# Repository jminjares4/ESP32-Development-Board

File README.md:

# ESP32-Development-Board
## ESP32 2 Layer PCB
* The PCB was developed in KiCad. With the use of https://github.com/wokwi/kicad-jlcpcb-bom-plugin, 
* Use the 'python3' kicad_pos_to_cpl.py to convert KiCad CPL files to JLCPCB 
## BOM
* This folder contains the BOM file for JLCPCB for the ESP32. 
## ESP32 CPL File
* This folder contains the CPL file for ESP32
 ### JLCPCB_File
  *  JLCPCB csv file configuration for ESP32 dev board
 ### KiCad_Pos
  * KiCad default position file for ESP32 dev board

## KiCad ESP32 Schematic

### ESP32 Frontview

### ESP32 Backview

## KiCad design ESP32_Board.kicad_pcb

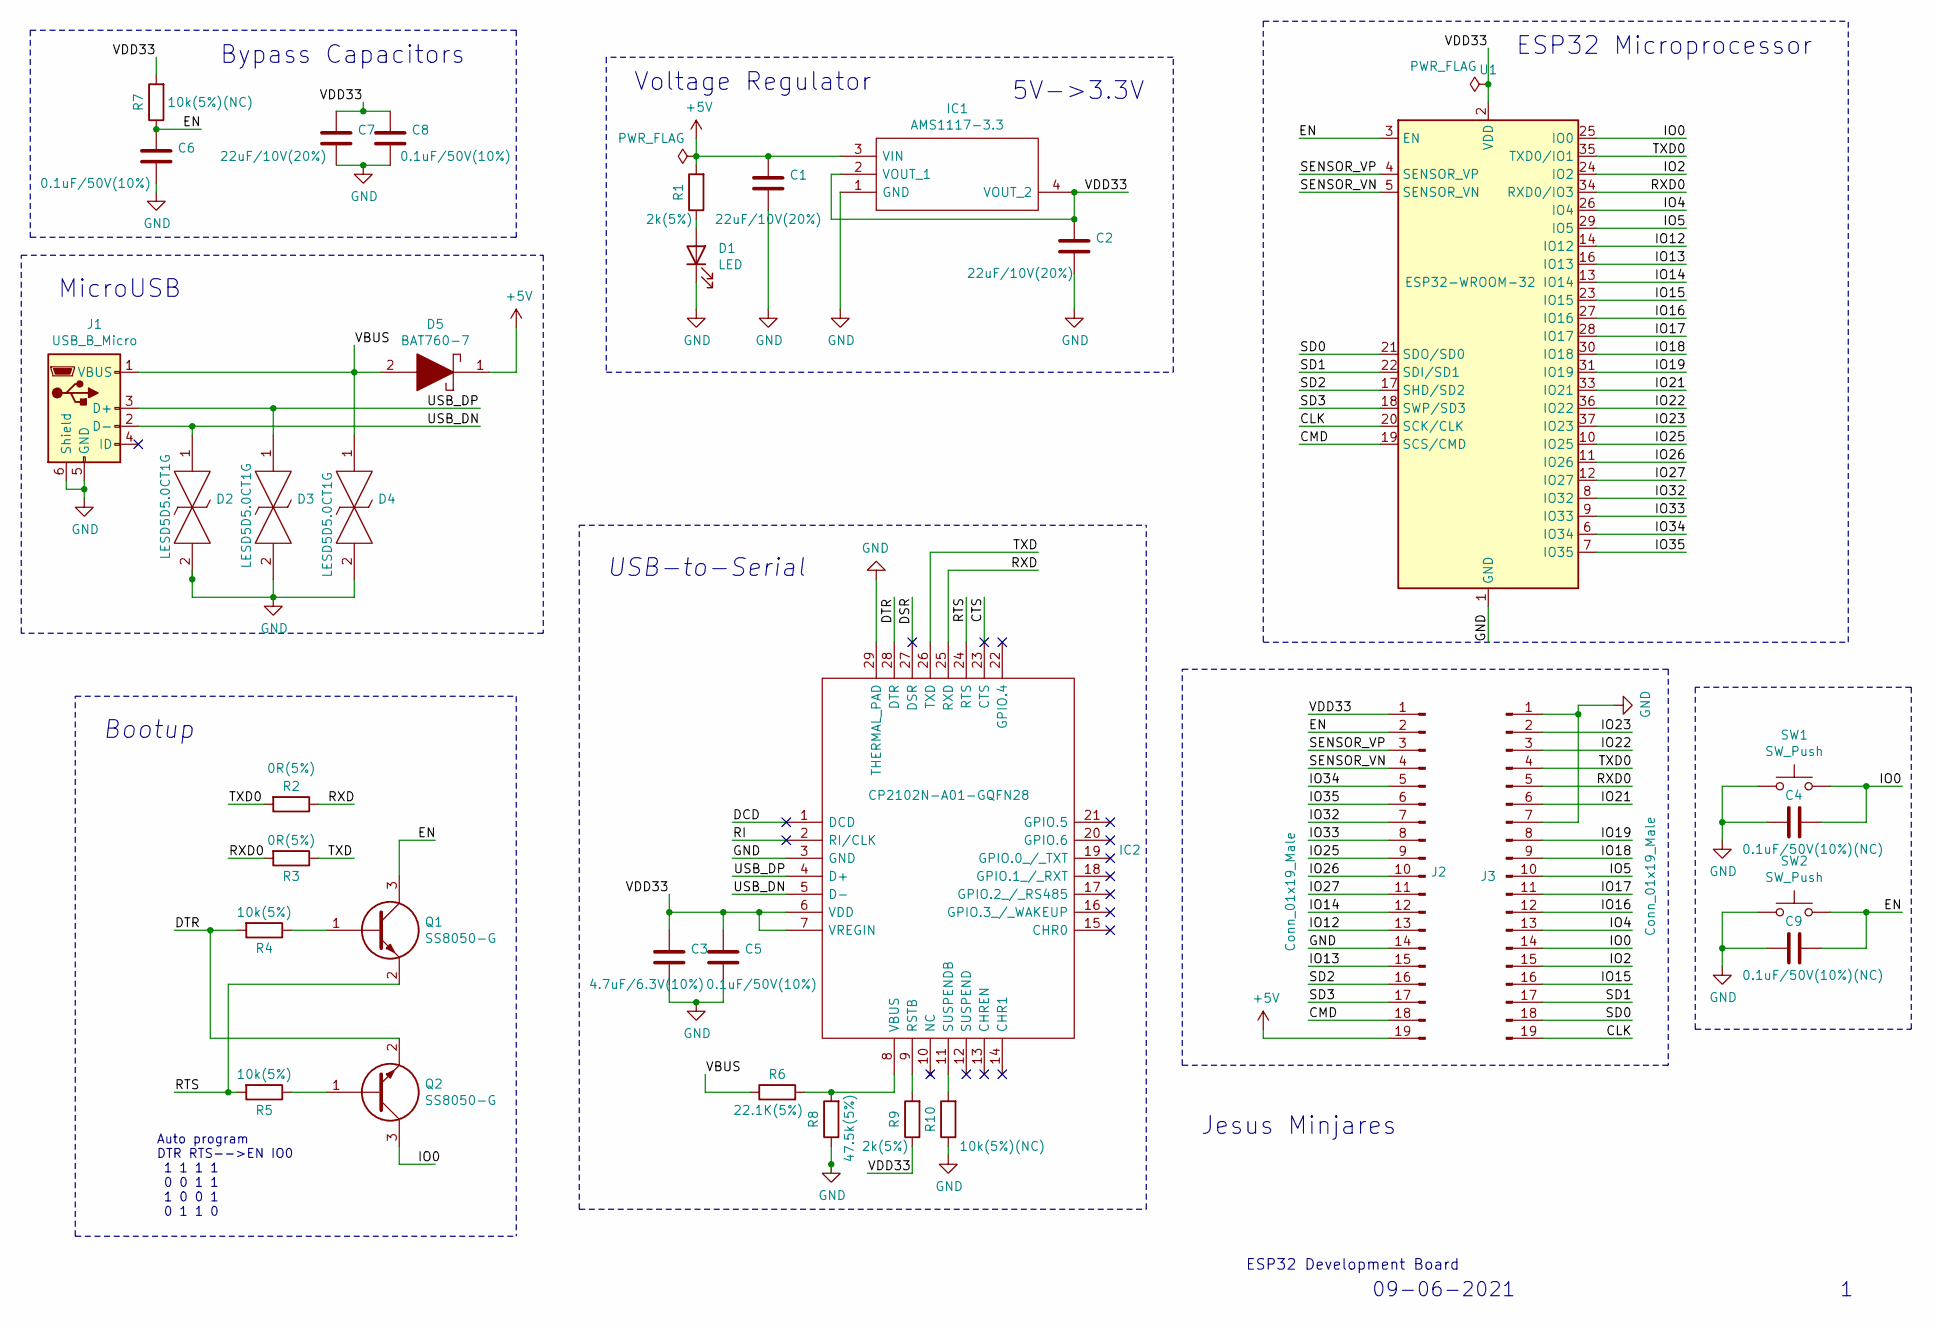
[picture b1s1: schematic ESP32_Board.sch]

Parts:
C1, C2, C7: 22uF/10V(20%); C_0805_2012Metric
C3: 4.7uF/6.3V(10%); C_0805_2012Metric
C4, C9: 0.1uF/50V(10%)(NC); C_0805_2012Metric
C5, C6, C8: 0.1uF/50V(10%); C_0805_2012Metric
D1: LED; LED_0805_2012Metric
D2, D3, D4: LESD5D5.0CT1G; LESD5D50CT1G; Manufacturer_Part_Number LESD5D5.0CT1G
D5: BAT760-7; SOD2513X120N; Manufacturer_Part_Number BAT760-7; Mouser Part Number 621-BAT760-7
IC1: AMS1117-3.3; SOT229P700X180-4N; Manufacturer_Part_Number AMS1117-3.3
IC2: CP2102N-A01-GQFN28; QFN50P500X500X80-29N-D; Manufacturer_Part_Number CP2102N-A01-GQFN28; Mouser Part Number 634-CP2102NA01GQFN28
J1: USB_B_Micro; USB_Micro-B_Amphenol_10103594-0001LF_Horizontal
J2, J3: Conn_01x19_Male; PinHeader_1x19_P2.54mm_Vertical
Q1, Q2: SS8050-G; SOT95P240X115-3N; Manufacturer_Part_Number SS8050-G; Mouser Part Number 750-SS8050-G
R1, R9: 2k(5%); R_0805_2012Metric
R2, R3: 0R(5%); R_0805_2012Metric
R4, R5: 10k(5%); R_0805_2012Metric
R6: 22.1K(5%); R_0805_2012Metric
R7, R10: 10k(5%)(NC); R_0805_2012Metric
R8: 47.5k(5%); R_0805_2012Metric
SW1, SW2: SW_Push; SW_SPST_B3U-1000P
U1: ESP32-WROOM-32

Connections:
+5V: C1.1, D5.1, IC1.3 (VIN), J2.19, R1.2
/CLK: J3.19, U1.20 (SCK/CLK)
/CMD: J2.18, U1.19 (SCS/CMD)
/CTS: IC2.23 (CTS)
/DCD: IC2.1 (DCD)
/DSR: IC2.27 (DSR)
/DTR: IC2.28 (DTR), Q2.2, R4.2
/EN: C6.1, C9.2, J2.2, Q1.3, R7.1, SW2.2, U1.3 (EN)
/IO0: C4.2, J3.14, Q2.3, SW1.2, U1.25 (IO0)
/IO2: J3.15, U1.24 (IO2)
/IO4: J3.13, U1.26 (IO4)
/IO5: J3.10, U1.29 (IO5)
/IO12: J2.13, U1.14 (IO12)
/IO13: J2.15, U1.16 (IO13)
/IO14: J2.12, U1.13 (IO14)
/IO15: J3.16, U1.23 (IO15)
/IO16: J3.12, U1.27 (IO16)
/IO17: J3.11, U1.28 (IO17)
/IO18: J3.9, U1.30 (IO18)
/IO19: J3.8, U1.31 (IO19)
/IO21: J3.6, U1.33 (IO21)
/IO22: J3.3, U1.36 (IO22)
/IO23: J3.2, U1.37 (IO23)
/IO25: J2.9, U1.10 (IO25)
/IO26: J2.10, U1.11 (IO26)
/IO27: J2.11, U1.12 (IO27)
/IO32: J2.7, U1.8 (IO32)
/IO33: J2.8, U1.9 (IO33)
/IO34: J2.5, U1.6 (IO34)
/IO35: J2.6, U1.7 (IO35)
/RI: IC2.2 (RI/CLK)
/RTS: IC2.24 (RTS), Q1.2, R5.2
/RXD: IC2.25 (RXD), R2.1
/RXD0: J3.5, R3.2, U1.34 (RXD0/IO3)
/SD0: J3.18, U1.21 (SDO/SD0)
/SD1: J3.17, U1.22 (SDI/SD1)
/SD2: J2.16, U1.17 (SHD/SD2)
/SD3: J2.17, U1.18 (SWP/SD3)
/SENSOR_VN: J2.4, U1.5 (SENSOR_VN)
/SENSOR_VP: J2.3, U1.4 (SENSOR_VP)
/TXD: IC2.26 (TXD), R3.1
/TXD0: J3.4, R2.2, U1.35 (TXD0/IO1)
/USB_DN: D2.1, IC2.5 (D-), J1.2 (D-)
/USB_DP: D3.1, IC2.4 (D+), J1.3 (D+)
/VBUS: D4.1, D5.2, J1.1 (VBUS), R6.1
/VDD33: C2.1, C3.1, C5.1, C7.1, C8.1, IC1.2 (VOUT_1), IC1.4 (VOUT_2), IC2.6 (VDD), IC2.7 (VREGIN), J2.1, R7.2, R9.1, U1.2 (VDD)
GND: C1.2, C2.2, C3.2, C4.1, C5.2, C6.2, C7.2, C8.2, C9.1, D1.1 (K), D2.2, D3.2, D4.2, IC1.1 (GND), IC2.3 (GND), IC2.29 (THERMAL_PAD), J1.5 (GND), J1.6 (Shield), J2.14, J3.1, J3.7, R8.1, R10.1, SW1.1, SW2.1, U1.1 (GND), U1.15 (GND), U1.38 (GND), U1.39 (GND)
unnamed: D1.2 (A), R1.1
unnamed: IC2.8 (VBUS), R6.2, R8.2
unnamed: IC2.9 (RSTB), R9.2
unnamed: IC2.11 (SUSPENDB), R10.2
unnamed: Q1.1, R4.1
unnamed: Q2.1, R5.1

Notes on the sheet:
Auto program DTR RTS-->EN IO0 1 1 1 1 0 0 1 1 1 0 0 1 0 1 1 0
USB-to-Serial
Bootup
MicroUSB
Bypass Capacitors
Voltage Regulator
5V->3.3V
ESP32 Microprocessor
Jesus Minjares
ESP32 Development Board
09-06-2021

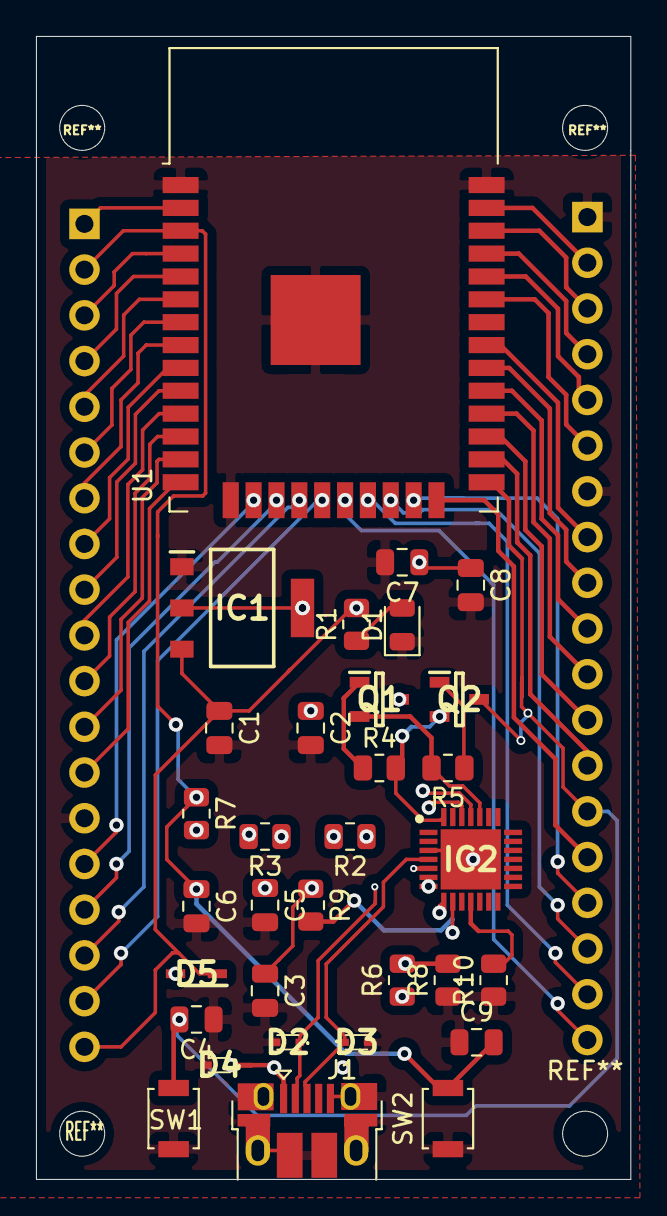
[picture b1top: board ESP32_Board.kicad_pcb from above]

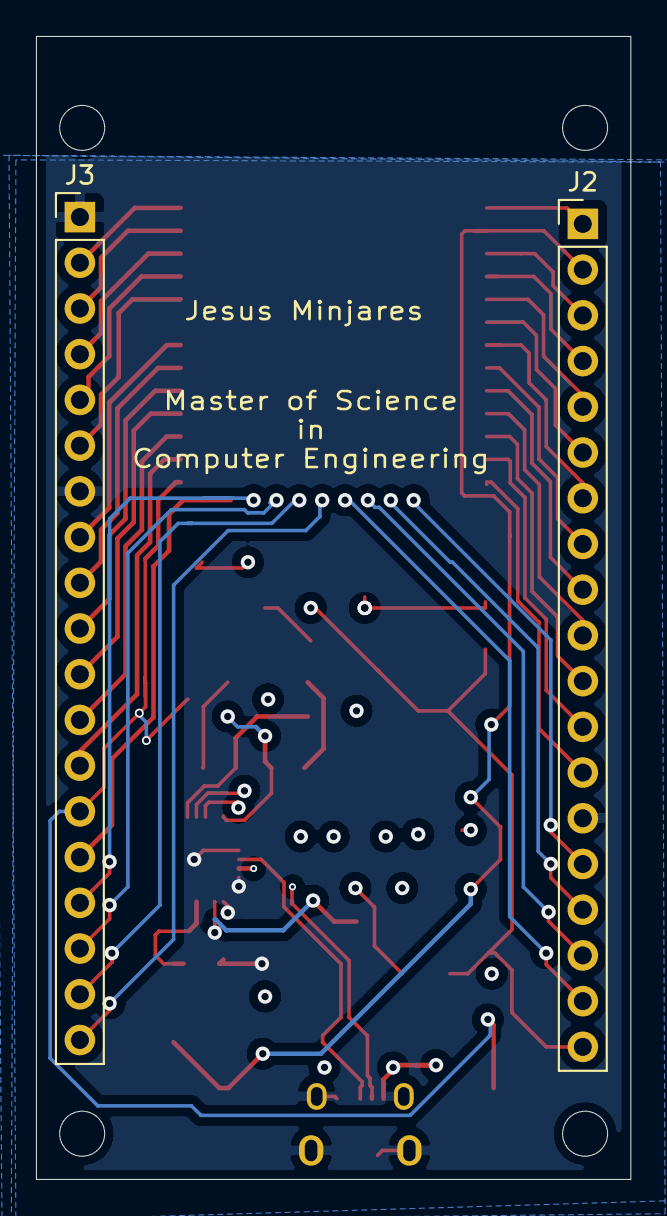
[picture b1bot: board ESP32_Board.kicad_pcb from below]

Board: 4 copper layers, 33.0 x 63.5 mm, 34 parts (2 on the bottom side), 49 nets.

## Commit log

2021-09-20 ESP32 KiCad Project
2021-10-09 Editing PCB
2021-10-09 Added README.md
2021-10-11 2 Layer PCB
2021-10-11 Update ESP32 PCB to 2 Layers
